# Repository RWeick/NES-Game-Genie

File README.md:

# NES-Game-Genie
The Kicad files and rom dump of the NES Game Genie (DIP Version)

PCB Thickness: 1.6 mm

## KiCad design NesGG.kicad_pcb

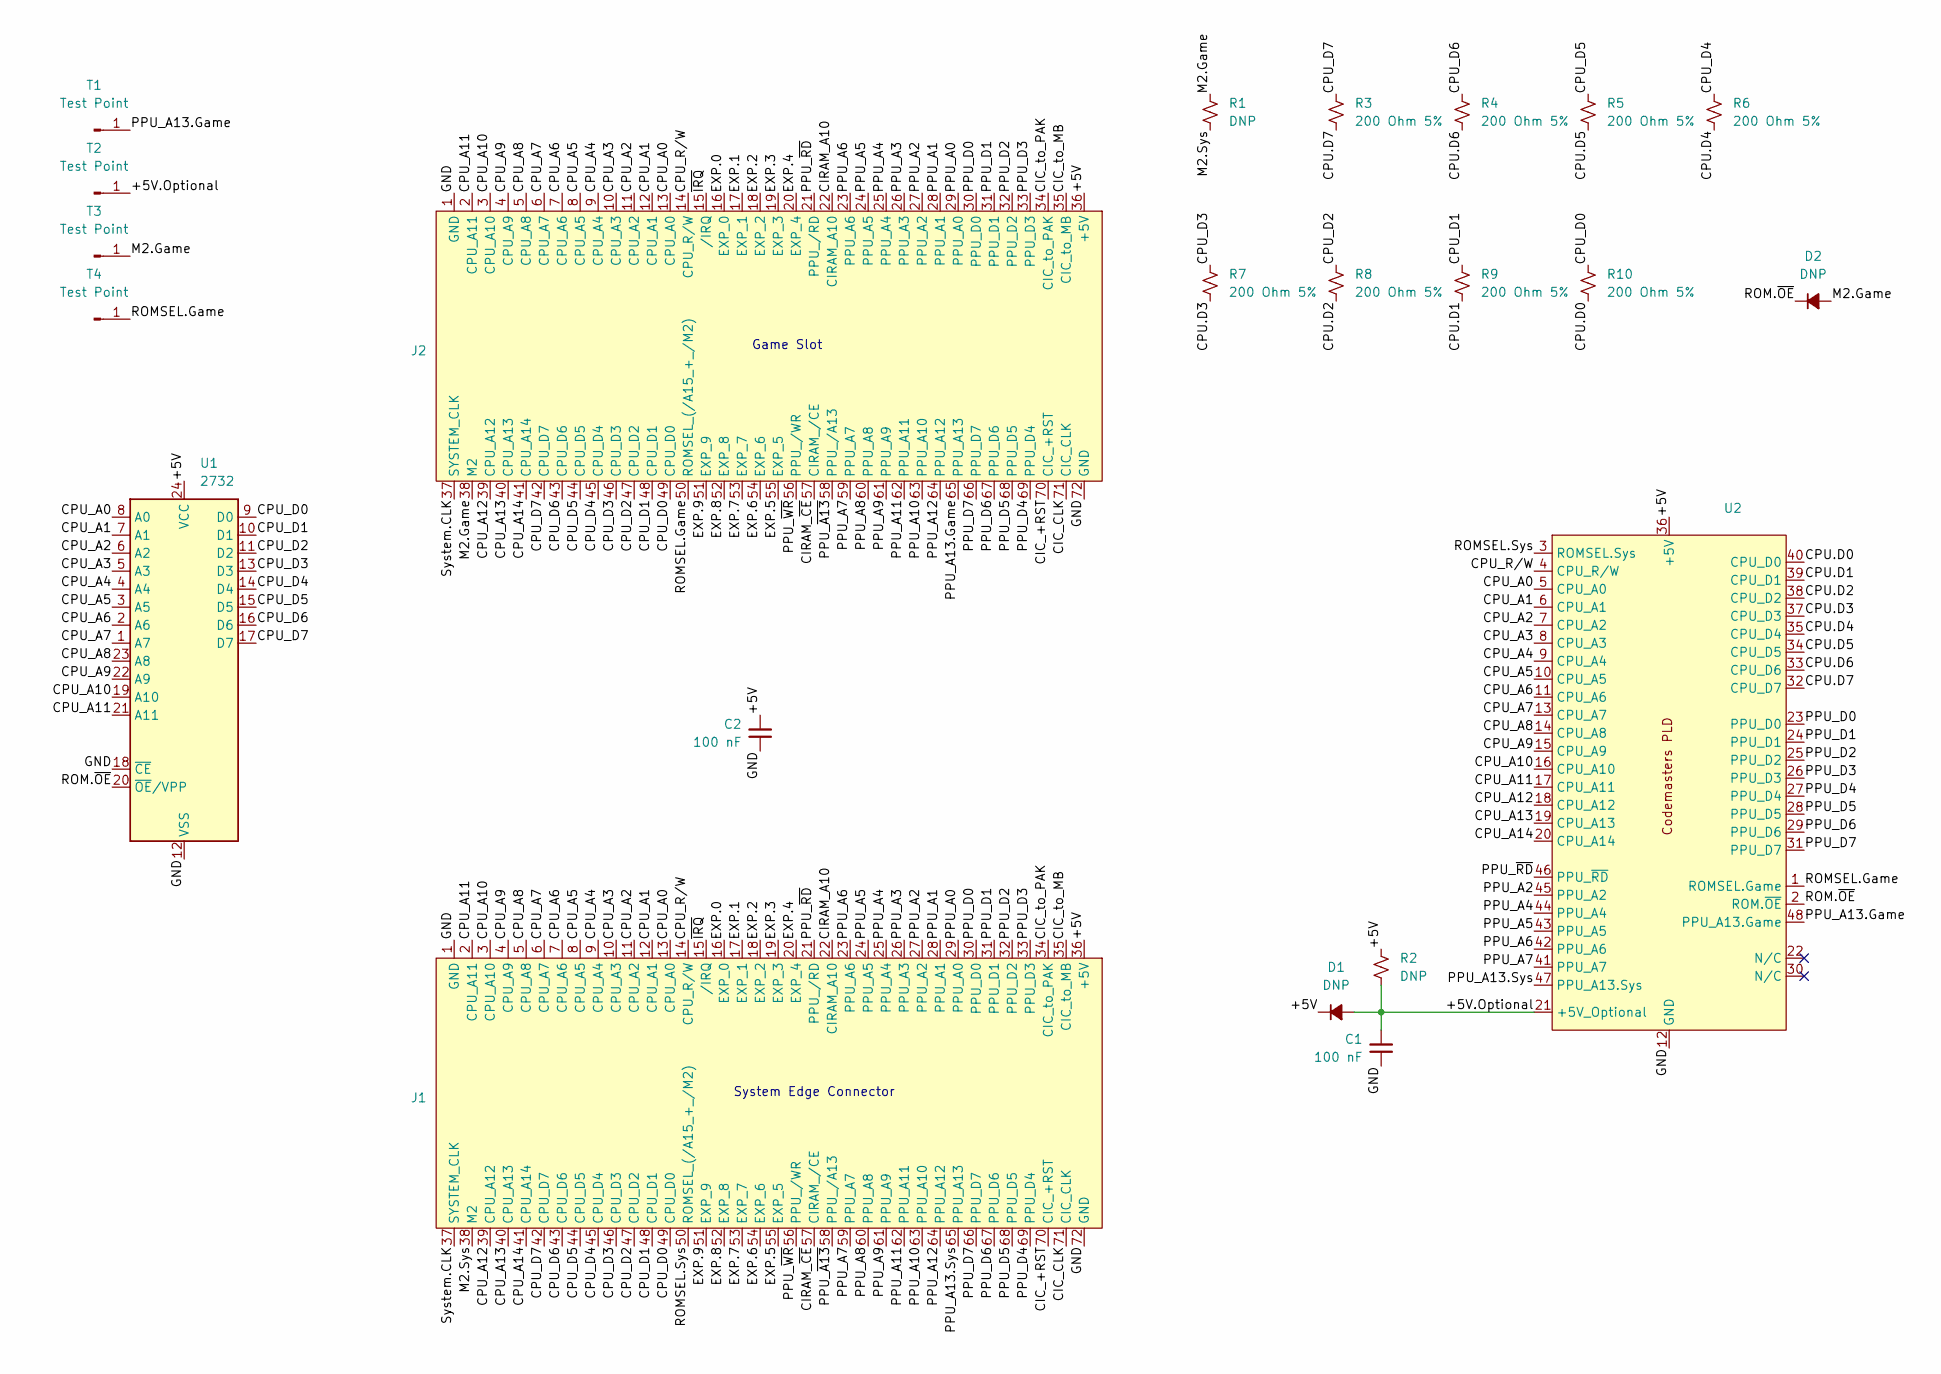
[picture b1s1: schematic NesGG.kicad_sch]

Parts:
C1, C2: 100 nF; Capacitor
D1, D2: DNP; Diode
J1: Edge Connector
J2: Cartridge Slot
R1, R2: DNP; Resistor
R3, R4, R5, R6, R7, R8, R9, R10: 200 Ohm 5%; Resistor
T1, T2, T3, T4: Test Point
U1: 2732
U2: CODEMASTERS PLD

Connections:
/+5V: C2.2, D1.1 (K), J1.36 (+5V), J2.36 (+5V), R2.1, U1.24 (VCC), U2.36 (+5V)
/+5V.Optional: C1.2, D1.2 (A), R2.2, T2.1, U2.21 (+5V_Optional)
/CIC_+RST: J1.70 (CIC_+RST), J2.70 (CIC_+RST)
/CIC_CLK: J1.71 (CIC_CLK), J2.71 (CIC_CLK)
/CIC_to_MB: J1.35 (CIC_to_MB), J2.35 (CIC_to_MB)
/CIC_to_PAK: J1.34 (CIC_to_PAK), J2.34 (CIC_to_PAK)
/CIRAM_A10: J1.22 (CIRAM_A10), J2.22 (CIRAM_A10)
/CIRAM_~CE: J1.57 (CIRAM_/CE), J2.57 (CIRAM_/CE)
/CPU.D0: R10.2, U2.40 (CPU_D0)
/CPU.D1: R9.2, U2.39 (CPU_D1)
/CPU.D2: R8.2, U2.38 (CPU_D2)
/CPU.D3: R7.2, U2.37 (CPU_D3)
/CPU.D4: R6.2, U2.35 (CPU_D4)
/CPU.D5: R5.2, U2.34 (CPU_D5)
/CPU.D6: R4.2, U2.33 (CPU_D6)
/CPU.D7: R3.2, U2.32 (CPU_D7)
/CPU_A0: J1.13 (CPU_A0), J2.13 (CPU_A0), U1.8 (A0), U2.5 (CPU_A0)
/CPU_A1: J1.12 (CPU_A1), J2.12 (CPU_A1), U1.7 (A1), U2.6 (CPU_A1)
/CPU_A2: J1.11 (CPU_A2), J2.11 (CPU_A2), U1.6 (A2), U2.7 (CPU_A2)
/CPU_A3: J1.10 (CPU_A3), J2.10 (CPU_A3), U1.5 (A3), U2.8 (CPU_A3)
/CPU_A4: J1.9 (CPU_A4), J2.9 (CPU_A4), U1.4 (A4), U2.9 (CPU_A4)
/CPU_A5: J1.8 (CPU_A5), J2.8 (CPU_A5), U1.3 (A5), U2.10 (CPU_A5)
/CPU_A6: J1.7 (CPU_A6), J2.7 (CPU_A6), U1.2 (A6), U2.11 (CPU_A6)
/CPU_A7: J1.6 (CPU_A7), J2.6 (CPU_A7), U1.1 (A7), U2.13 (CPU_A7)
/CPU_A8: J1.5 (CPU_A8), J2.5 (CPU_A8), U1.23 (A8), U2.14 (CPU_A8)
/CPU_A9: J1.4 (CPU_A9), J2.4 (CPU_A9), U1.22 (A9), U2.15 (CPU_A9)
/CPU_A10: J1.3 (CPU_A10), J2.3 (CPU_A10), U1.19 (A10), U2.16 (CPU_A10)
/CPU_A11: J1.2 (CPU_A11), J2.2 (CPU_A11), U1.21 (A11), U2.17 (CPU_A11)
/CPU_A12: J1.39 (CPU_A12), J2.39 (CPU_A12), U2.18 (CPU_A12)
/CPU_A13: J1.40 (CPU_A13), J2.40 (CPU_A13), U2.19 (CPU_A13)
/CPU_A14: J1.41 (CPU_A14), J2.41 (CPU_A14), U2.20 (CPU_A14)
/CPU_D0: J1.49 (CPU_D0), J2.49 (CPU_D0), R10.1, U1.9 (D0)
/CPU_D1: J1.48 (CPU_D1), J2.48 (CPU_D1), R9.1, U1.10 (D1)
/CPU_D2: J1.47 (CPU_D2), J2.47 (CPU_D2), R8.1, U1.11 (D2)
/CPU_D3: J1.46 (CPU_D3), J2.46 (CPU_D3), R7.1, U1.13 (D3)
/CPU_D4: J1.45 (CPU_D4), J2.45 (CPU_D4), R6.1, U1.14 (D4)
/CPU_D5: J1.44 (CPU_D5), J2.44 (CPU_D5), R5.1, U1.15 (D5)
/CPU_D6: J1.43 (CPU_D6), J2.43 (CPU_D6), R4.1, U1.16 (D6)
/CPU_D7: J1.42 (CPU_D7), J2.42 (CPU_D7), R3.1, U1.17 (D7)
/CPU_R/W: J1.14 (CPU_R/W), J2.14 (CPU_R/W), U2.4 (CPU_R/W)
/EXP.0: J1.16 (EXP_0), J2.16 (EXP_0)
/EXP.1: J1.17 (EXP_1), J2.17 (EXP_1)
/EXP.2: J1.18 (EXP_2), J2.18 (EXP_2)
/EXP.3: J1.19 (EXP_3), J2.19 (EXP_3)
/EXP.4: J1.20 (EXP_4), J2.20 (EXP_4)
/EXP.5: J1.55 (EXP_5), J2.55 (EXP_5)
/EXP.6: J1.54 (EXP_6), J2.54 (EXP_6)
/EXP.7: J1.53 (EXP_7), J2.53 (EXP_7)
/EXP.8: J1.52 (EXP_8), J2.52 (EXP_8)
/EXP.9: J1.51 (EXP_9), J2.51 (EXP_9)
/GND: C1.1, C2.1, J1.1 (GND), J1.72 (GND), J2.1 (GND), J2.72 (GND), U1.12 (VSS), U1.18 (~CE), U2.12 (GND)
/M2.Game: D2.2 (A), J2.38 (M2), R1.1, T3.1
/M2.Sys: J1.38 (M2), R1.2
/PPU_A0: J1.29 (PPU_A0), J2.29 (PPU_A0)
/PPU_A1: J1.28 (PPU_A1), J2.28 (PPU_A1)
/PPU_A2: J1.27 (PPU_A2), J2.27 (PPU_A2), U2.45 (PPU_A2)
/PPU_A3: J1.26 (PPU_A3), J2.26 (PPU_A3)
/PPU_A4: J1.25 (PPU_A4), J2.25 (PPU_A4), U2.44 (PPU_A4)
/PPU_A5: J1.24 (PPU_A5), J2.24 (PPU_A5), U2.43 (PPU_A5)
/PPU_A6: J1.23 (PPU_A6), J2.23 (PPU_A6), U2.42 (PPU_A6)
/PPU_A7: J1.59 (PPU_A7), J2.59 (PPU_A7), U2.41 (PPU_A7)
/PPU_A8: J1.60 (PPU_A8), J2.60 (PPU_A8)
/PPU_A9: J1.61 (PPU_A9), J2.61 (PPU_A9)
/PPU_A10: J1.63 (PPU_A10), J2.63 (PPU_A10)
/PPU_A11: J1.62 (PPU_A11), J2.62 (PPU_A11)
/PPU_A12: J1.64 (PPU_A12), J2.64 (PPU_A12)
/PPU_A13.Game: J2.65 (PPU_A13), T1.1, U2.48 (PPU_A13.Game)
/PPU_A13.Sys: J1.65 (PPU_A13), U2.47 (PPU_A13.Sys)
/PPU_D0: J1.30 (PPU_D0), J2.30 (PPU_D0), U2.23 (PPU_D0)
/PPU_D1: J1.31 (PPU_D1), J2.31 (PPU_D1), U2.24 (PPU_D1)
/PPU_D2: J1.32 (PPU_D2), J2.32 (PPU_D2), U2.25 (PPU_D2)
/PPU_D3: J1.33 (PPU_D3), J2.33 (PPU_D3), U2.26 (PPU_D3)
/PPU_D4: J1.69 (PPU_D4), J2.69 (PPU_D4), U2.27 (PPU_D4)
/PPU_D5: J1.68 (PPU_D5), J2.68 (PPU_D5), U2.28 (PPU_D5)
/PPU_D6: J1.67 (PPU_D6), J2.67 (PPU_D6), U2.29 (PPU_D6)
/PPU_D7: J1.66 (PPU_D7), J2.66 (PPU_D7), U2.31 (PPU_D7)
/PPU_~A13: J1.58 (PPU_/A13), J2.58 (PPU_/A13)
/PPU_~RD: J1.21 (PPU_/RD), J2.21 (PPU_/RD), U2.46 (PPU_~RD)
/PPU_~WR: J1.56 (PPU_/WR), J2.56 (PPU_/WR)
/ROM.~OE: D2.1 (K), U1.20 (~OE/VPP), U2.2 (ROM.~OE)
/ROMSEL.Game: J2.50 (ROMSEL_(/A15_+_/M2)), T4.1, U2.1 (ROMSEL.Game)
/ROMSEL.Sys: J1.50 (ROMSEL_(/A15_+_/M2)), U2.3 (ROMSEL.Sys)
/System.CLK: J1.37 (SYSTEM_CLK), J2.37 (SYSTEM_CLK)
/~IRQ: J1.15 (/IRQ), J2.15 (/IRQ)

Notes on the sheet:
Game Slot
System Edge Connector

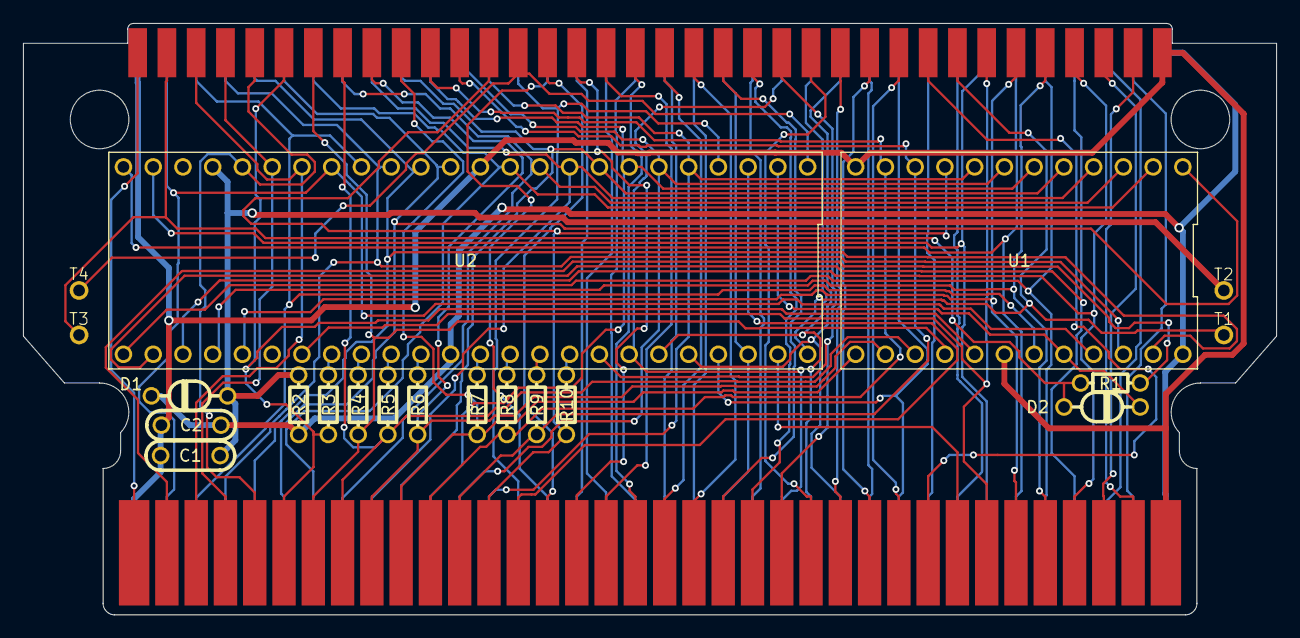
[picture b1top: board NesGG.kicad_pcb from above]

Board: 2 copper layers, 107.0 x 50.5 mm, 22 parts (0 on the bottom side), 84 nets.
